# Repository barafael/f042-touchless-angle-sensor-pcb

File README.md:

# f042-touchless-angle-sensor-pcb
Waterproof 180 degree touchless angle sensor using the f042

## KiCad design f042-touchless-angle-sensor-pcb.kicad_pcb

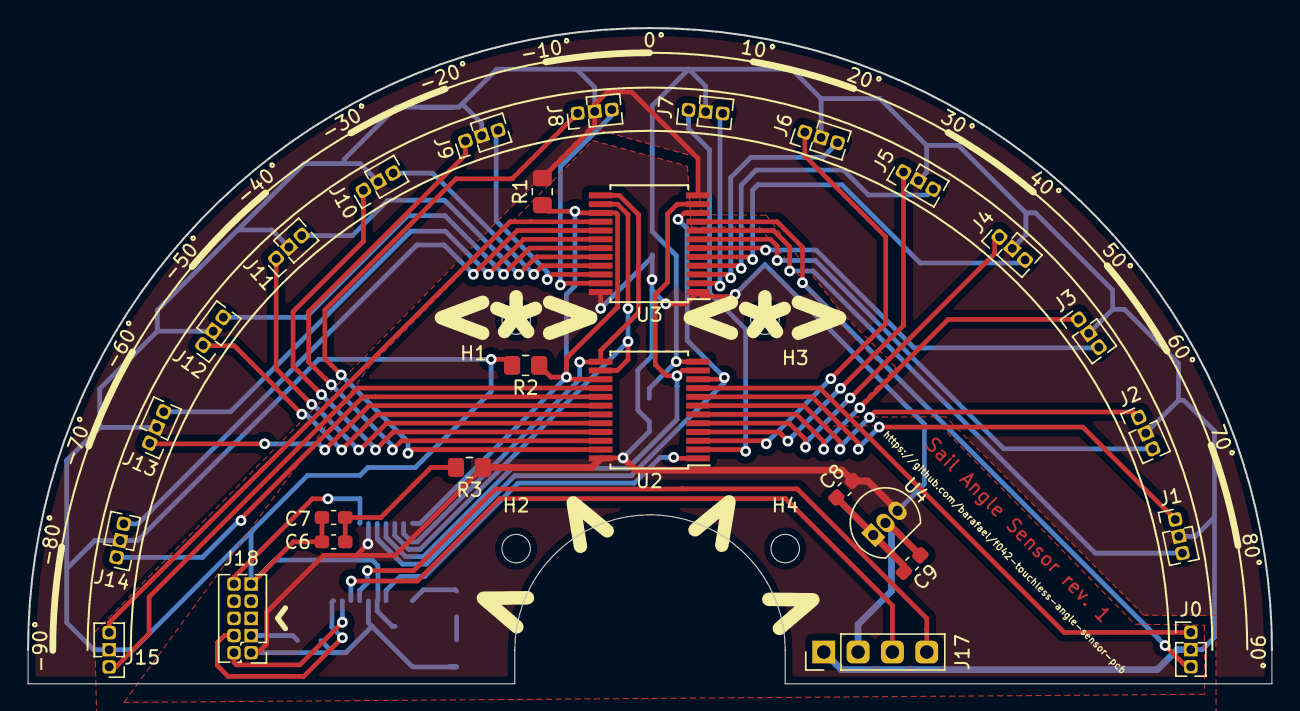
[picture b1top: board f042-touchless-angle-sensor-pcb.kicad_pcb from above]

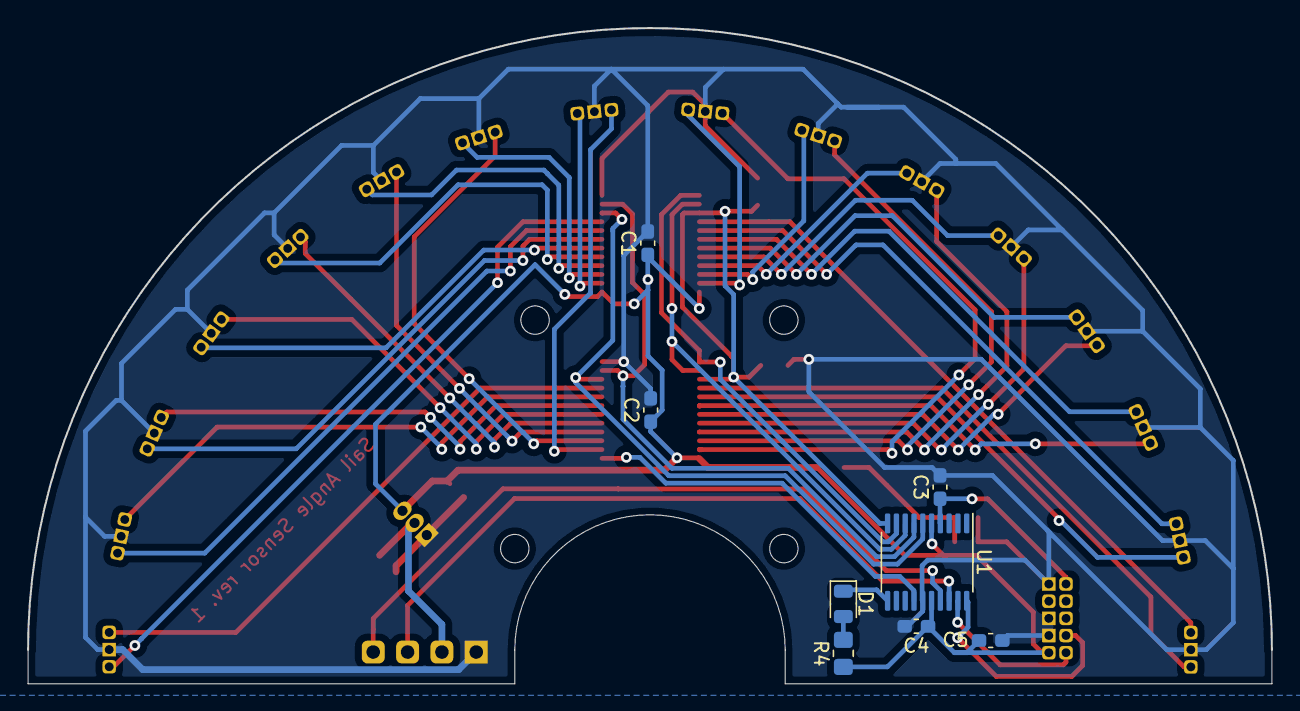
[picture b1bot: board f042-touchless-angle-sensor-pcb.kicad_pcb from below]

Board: 2 copper layers, 92.0 x 48.5 mm, 40 parts (8 on the bottom side), 49 nets.

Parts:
C1, C2: 0.1uF; C_0603_1608Metric_Pad1.08x0.95mm_HandSolder
C3, C4: 100nF; C_0603_1608Metric_Pad1.08x0.95mm_HandSolder
C5: 4.7uF; C_0603_1608Metric_Pad1.08x0.95mm_HandSolder
C6: 10nF; C_0603_1608Metric_Pad1.08x0.95mm_HandSolder
C7, C8, C9: 1uF; C_0603_1608Metric_Pad1.08x0.95mm_HandSolder
D1: LED; LED_0805_2012Metric
H1, H2, H3, H4: MountingHole; MountingHole_2.1mm
J0, J1, J2, J3, J4, J5, J6, J7, J8, J9, J10, J11, J12, J13, J14, J15: Conn_01x03; PinHeader_1x03_P1.27mm_Vertical
J17: Conn_01x04; PinHeader_1x04_P2.54mm_Vertical
J18: Conn_02x05_Odd_Even; PinHeader_2x05_P1.27mm_Vertical
R1, R2: 10K; R_0805_2012Metric_Pad1.20x1.40mm_HandSolder
R3: 0; R_0805_2012Metric_Pad1.20x1.40mm_HandSolder
R4: R; R_0805_2012Metric_Pad1.20x1.40mm_HandSolder
U1: STM32F042F6Px; TSSOP-20_4.4x6.5mm_P0.65mm
U2, U3: CD74HC4067SM; SSOP-24_5.3x8.2mm_P0.65mm
U4: MCP1700-3302E_TO92; TO-92_Inline

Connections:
EN: R1.1, R2.1, U1.10, U2.15, U3.15
GND: C1.2, C2.2, C3.2, C4.2, C5.2, C6.2, C7.2, C8.2, C9.2, J0.2, J1.2, J2.2, J3.2, J4.2, J5.2, J6.2, J7.2, J8.2, J9.2, J10.2, J11.2, J12.2, J13.2, J14.2, J15.2, J17.1, J18.3, J18.5, J18.9, R1.2, R2.2, U1.15, U2.12, U3.12, U4.1
LED: D1.1, U1.11
NRST: C3.1, J18.10, U1.4
unnamed: D1.2, R4.2
SEL0: U1.6, U2.10, U3.10
SEL1: U1.7, U2.11, U3.11
SEL2: U1.8, U2.14, U3.14
SEL3: U1.9, U2.13, U3.13
SENSE: U1.14, U2.1
SENSE0: J0.1, U2.9
SENSE1: J1.1, U2.8
SENSE2: J2.1, U2.7
SENSE3: J3.1, U2.6
SENSE4: J4.1, U2.5
SENSE5: J5.1, U2.4
SENSE6: J6.1, U2.3
SENSE7: J7.1, U2.2
SENSE8: J8.1, U2.23
SENSE9: J9.1, U2.22
SENSE10: J10.1, U2.21
SENSE11: J11.1, U2.20
SENSE12: J12.1, U2.19
SENSE13: J13.1, U2.18
SENSE14: J14.1, U2.17
SENSE15: J15.1, U2.16
SENSOR_SUPPLY0: J0.3, U3.9
SENSOR_SUPPLY1: J1.3, U3.8
SENSOR_SUPPLY2: J2.3, U3.7
SENSOR_SUPPLY3: J3.3, U3.6
SENSOR_SUPPLY4: J4.3, U3.5
SENSOR_SUPPLY5: J5.3, U3.4
SENSOR_SUPPLY6: J6.3, U3.3
SENSOR_SUPPLY7: J7.3, U3.2
SENSOR_SUPPLY8: J8.3, U3.23
SENSOR_SUPPLY9: J9.3, U3.22
SENSOR_SUPPLY10: J10.3, U3.21
SENSOR_SUPPLY11: J11.3, U3.20
SENSOR_SUPPLY12: J12.3, U3.19
SENSOR_SUPPLY13: J13.3, U3.18
SENSOR_SUPPLY14: J14.3, U3.17
SENSOR_SUPPLY15: J15.3, U3.16
SERIAL_RX: J17.3, U1.18
SERIAL_TX: J17.4, U1.17
SWCLK: J18.4, U1.20
SWDIO: J18.2, U1.19
VDD: C1.1, C2.1, C4.1, C5.1, C8.1, J18.1, R3.1, R4.1, U1.5, U1.16, U2.24, U3.1, U3.24, U4.3
VDD_ANALOG: C6.1, C7.1, R3.2
VIN: C9.1, J17.2, U4.2

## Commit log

2021-02-12 Add images
2021-02-12 Add schematic
2021-02-12 Rename files
2021-02-13 Improve layout
2021-02-15 Remove VDDA voltage divider
2021-03-18 Add labels
